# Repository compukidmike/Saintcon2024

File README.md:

# Saintcon 2024

## We found an old engineering drawing from MK Factor. It looks like someone did some reverse engineering on the original Klippy-Net Wrist Communicator. I wonder if we can use this in our fight against the evil Klippy AI...

## We also came across this press release...

## In all seriousness...
We don't normally release badge information before the conference, but we have some exciting new things this year and we want people to have the opportunity to make some cool additions to the badge.

## Klip-ons
You may have noticed in the "Engineering Drawing" above that the screws are labeled 3V3 and GND. The idea is that you can make "klip-on" (get it? Klippy.. Klip-on.. Yeah you get it) boards that get power from the screws that attach them to the badge.

We've provided KiCad libraries to help you get started (You'll find them in the Klip-ons directory).  
There's a schematic symbol for the power connections and 4 footprints for Left/Right/Upper/Lower Klip-ons. The footprints include the outline of the top of the badge for reference, as well as a simple board outline. You can remove it if you'd like to make your own shape. Just be sure to avoid covering the screen on the badge. The footprints also have keepout areas to help you avoid putting parts on the bottom side of your klip-on where it would interfere with the badge itself.

<b>Please note that the screen opening is NOT centered on the badge.</b> That was a huge oversight on my part but now we're stuck with it. That's why the KiCad footprints include an outline of the entire top of the badge with the screen opening. This becomes an issue because the badge can be flipped over to wear it on the other wrist. Please try to make your klip-ons not interfere with the screen opening in either orientation.

## Wrist Mount
We wanted to do something different this year, so this baby is wrist mounted! We'll provide a soft wristband (sweatband) that has velcro on it. If you'd like to wear your badge on your wrist, simply attach the other side of the velcro to the back of your badge. If you'd prefer to stick with a lanyard, we've got a plan for that as well.

The wristband will have the "rough" hook side of the velcro and the badge will have the soft loop side. This will hopefully avoid shirt damage if you decide to switch to lanyard mount during the conference.

## Minibadges
Every badge will come with a two-slot minibadge klip-on board similar to the one in the drawing. If you'd like to make your own minibadge klip-on board, you can find an example KiCad board in the Klip-ons directory. You can add more minibadge slots, but we suggest that you only connect the I2C lines to two slots. The badge only supports two official game minibadges at a time and they must be in the two slots that are connected to I2C. You can add more minibadge slots that just have power for displaying extra minibadges.

If you decide to make your own minibadge klip-on, you may notice that the I2C lines are labeled funny. This was done to cut down on the number of wires needed to connect the minibadges. Please keep the I2C connections as they are in the schematic so that your board will work. If you have questions about your board, feel free to reach out on discord and we'd be happy to look at it.

## Minibadge Extensions
We're sure some of you noticed that the "standard" 20-Pin minibadge extension connector isn't anywhere to be found on this badge. Rest assured that we didn't forget/abandon it (yet). Every badge will come with a minibadge expansion board that has a spot for the 20-Pin connector. It will have 8 minibadge slots and go on a lanyard like previous badges. *"But how will it be powered?,"* we hear you asking... well, that USB-C port on the badge happens to be able to supply power! There's no guarantee that the battery will last very long when you connect all the blinky lights, but that's the price you pay for wanting to blind everyone with your awesomeness!  
NOTE: The minibadge expansion board will NOT have I2C connected to the badge.

## But I don't know how to create a circuit board
Neither did we when we started. Everyone starts somewhere and there are resources to get you making circuit boards in no time! The software is all free/open source and we even have some video tutorials! 

### Videos
https://www.youtube.com/watch?v=kkLfmo14oiQ  
https://www.youtube.com/watch?v=oAkId60DOd4  
https://www.youtube.com/watch?v=VVd4cdz-lU0  

### Software
https://www.kicad.org/  
https://inkscape.org/  

# Now go create something awesome!
If you run into any problems or have questions, please reach out on the Saintcon discord.

# FAQs
<b>Q: What more information can you tell me about the badge?</b>  
A: I'm afraid what has been released, is what you get. It's more than you normally see anyway.  

<b>Q: But, I really want to do X with the badge, can I do it?</b>  
A: Again, if it works with what has been released, you bet. Go nuts  

<b>Q: Ok, but I REALLY want to have my minibadge interface with the badge game and do something special.</b>  
A: That's not a question, but let's start with the first bit there. Who told you there was a "game"?  

<b>Q: Oh...uhh...I suppose...I just assumed.</b>  
A: Again, not a question...you know how these work right?  

<b>Q: Why can't you support {super cool integration} it'll be awesome!</b>  
A: I'm sure it would be! The reality of the situation is trying to coordinate yours (and everyone elses) cool integrations puts a tremendous amount of stress / work on a small volunteer team that is already running at near capacity. Maybe in the future we'll have a cool framework / spec to make this seamless.but that's just not today.  

<b>Q: Ok, that's fair....so...is there a badge game or not?</b>  
A: ... Schmaybe ...  

<b>Q: Does v0rtex ever wear colors besides black?</b>  
A: Yes, once he wore a green shirt. It was a momentous occasion.  

<b>Q: What is the badge's team secret? What keeps them going?</b>  
A: Little Caesars pepperoni pizza puff thingies... If you haven't tried them...you really... actually...right now...order them. Then return and report.

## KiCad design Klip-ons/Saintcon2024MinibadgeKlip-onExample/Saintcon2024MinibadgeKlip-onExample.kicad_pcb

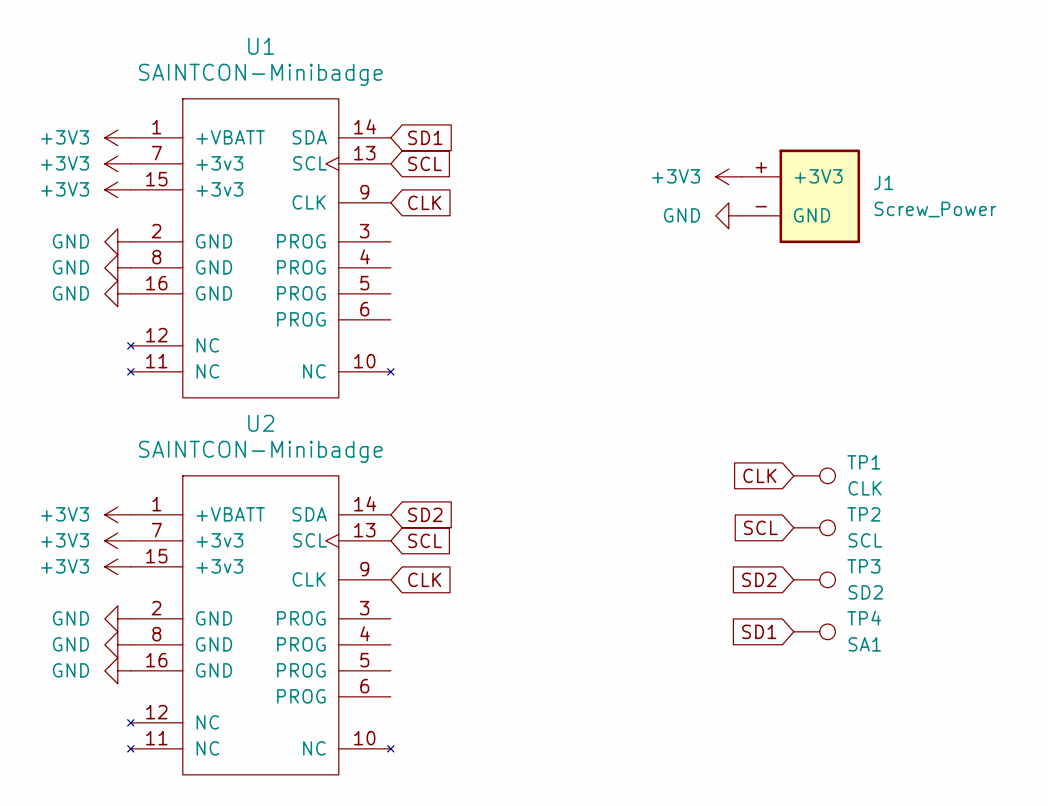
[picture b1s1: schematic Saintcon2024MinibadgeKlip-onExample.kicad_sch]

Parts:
J1: Screw_Power; Saintcon2024Klip-onLeft
TP1: CLK; TestPoint_THTPad_D2.0mm_Drill1.0mm
TP2: SCL; TestPoint_THTPad_D2.0mm_Drill1.0mm
TP3: SD2; TestPoint_THTPad_D2.0mm_Drill1.0mm
TP4: SA1; TestPoint_THTPad_D2.0mm_Drill1.0mm
U1, U2: SAINTCON-Minibadge; SAINTCON-Minibadge-Shiny

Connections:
+3V3: J1.+ (+3V3), U1.1 (+VBATT), U1.7 (+3v3), U1.15 (+3v3), U2.1 (+VBATT), U2.7 (+3v3), U2.15 (+3v3)
CLK: TP1.1, U1.9 (CLK), U2.9 (CLK)
GND: J1.- (GND), U1.2 (GND), U1.8 (GND), U1.16 (GND), U2.2 (GND), U2.8 (GND), U2.16 (GND)
SCL: TP2.1, U1.13 (SCL), U2.13 (SCL)
SD1: TP4.1, U1.14 (SDA)
SD2: TP3.1, U2.14 (SDA)

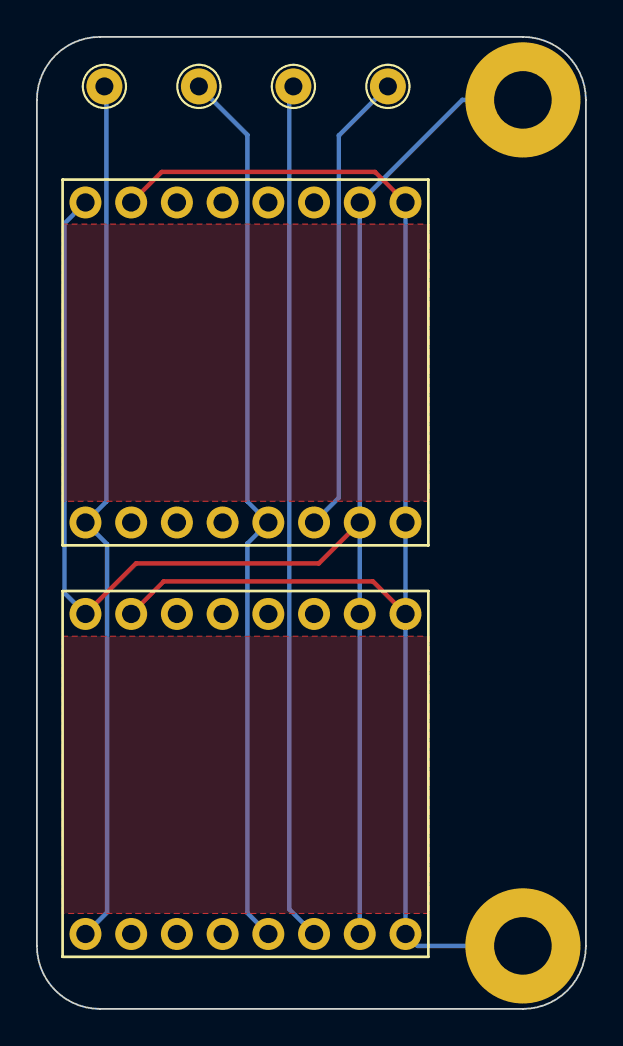
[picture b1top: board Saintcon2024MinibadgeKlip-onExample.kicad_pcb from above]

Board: 2 copper layers, 30.5 x 54.0 mm, 7 parts (0 on the bottom side), 6 nets.

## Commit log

2024-08-22 Add KiCad libraries and examples
2024-08-28 Update README.md
    Add FAQ
2024-11-12 Add Hardware Files
2025-02-07 Badge firmware
    This is the badge firmware in the current/latest form as of release
    version 2.6.9
